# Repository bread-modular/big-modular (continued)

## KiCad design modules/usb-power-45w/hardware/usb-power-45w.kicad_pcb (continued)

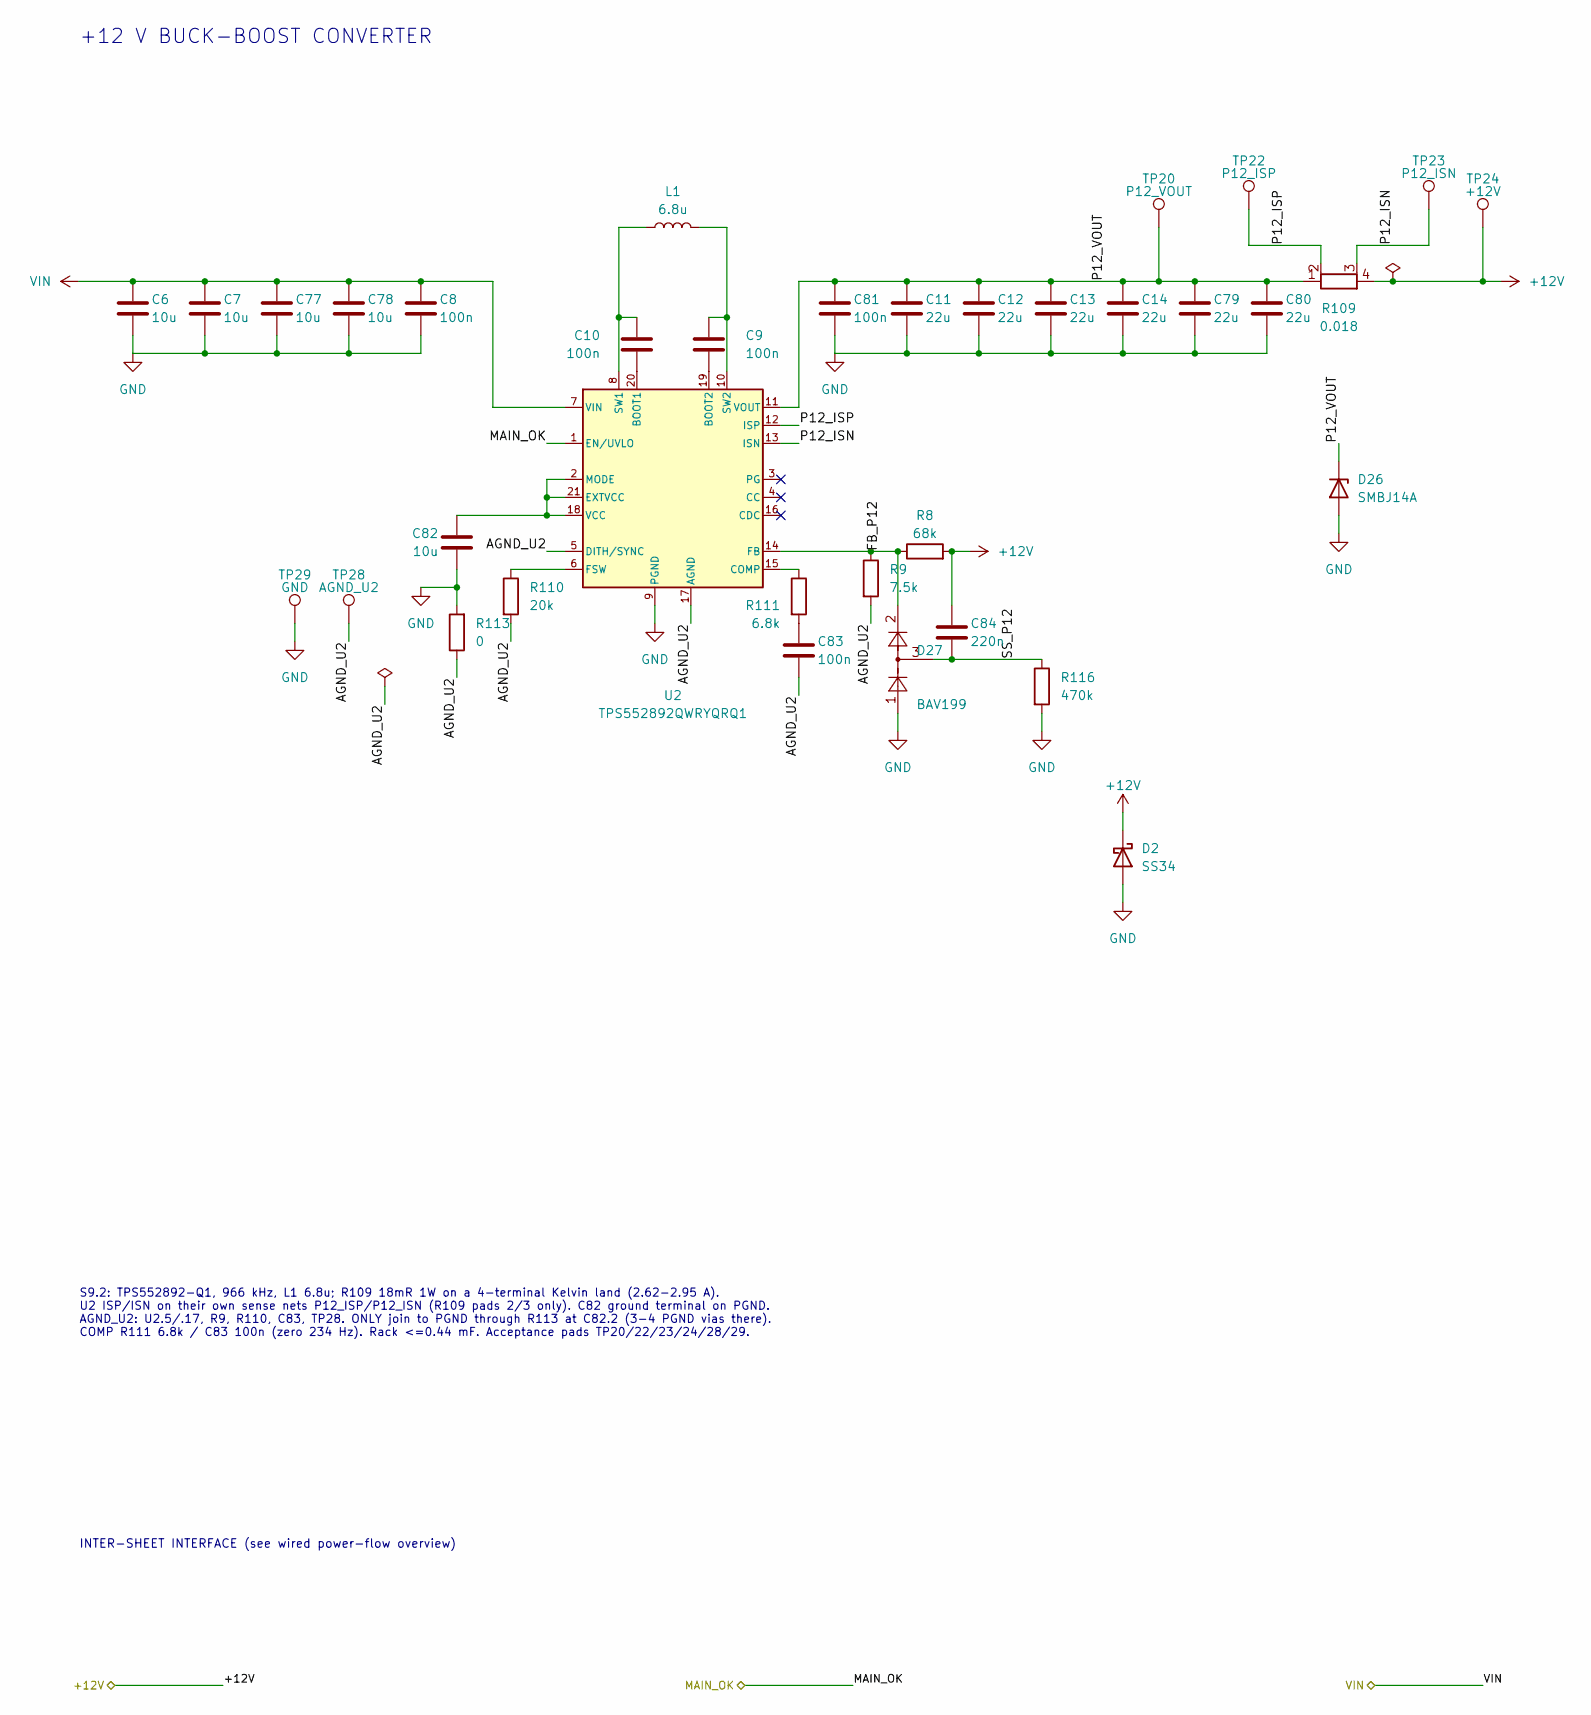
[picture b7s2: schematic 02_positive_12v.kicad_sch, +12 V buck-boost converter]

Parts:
C6, C7, C77, C78, C82: 10u; C_1206_3216Metric; Voltage 50V; MPN CL31A106KBHNNNE; LCSC C13585
C8, C9, C10, C81, C83: 100n; C_0603_1608Metric; Voltage 50V; MPN CC0603KRX7R9BB104; LCSC C14663
C11, C12, C13, C14, C79, C80: 22u; C_1206_3216Metric; Voltage 25V; MPN CL31A226KAHNNNE; LCSC C12891
C84: 220n; C_0603_1608Metric; Voltage 25V; MPN CL10B224KA8NNNC; LCSC C21120
D2: SS34; D_SMA; MPN SS34; LCSC C8678
D26: SMBJ14A; D_SMB; MPN SMBJ14A; LCSC C315990
D27: BAV199; SOT-23; MPN BAV199LT1G; LCSC C145516
L1: 6.8u; L_SLO1040H6R8MTT; MPN SLO1040H6R8MTT; LCSC C207852
R8: 68k; R_0603_1608Metric; Tolerance 1%; MPN 0603WAF6802T5E; LCSC C23231
R9: 7.5k; R_0603_1608Metric; Tolerance 1%; MPN 0603WAF7501T5E; LCSC C23234
R109: 0.018; R_Shunt_1206_KelvinSplit_RLM12; Tolerance 1%; MPN RLM12FTCMR018; LCSC C393095
R110: 20k; R_0603_1608Metric; Tolerance 1%; MPN 0603WAF2002T5E; LCSC C4184
R111: 6.8k; R_0603_1608Metric; Tolerance 1%; MPN 0603WAF6801T5E; LCSC C23212
R113: 0; R_0603_1608Metric; MPN 0603WAF0000T5E; LCSC C21189
R116: 470k; R_0603_1608Metric; Tolerance 1%; MPN 0603WAF4703T5E; LCSC C23178
TP20: P12_VOUT; TestPoint_Pad_D1.5mm
TP22: P12_ISP; TestPoint_Pad_D1.5mm
TP23: P12_ISN; TestPoint_Pad_D1.5mm
TP24: +12V; TestPoint_Pad_D1.5mm
TP28: AGND_U2; TestPoint_Pad_D1.5mm
TP29: GND; TestPoint_Pad_D1.5mm
U2: TPS552892QWRYQRQ1; TI_RYQ0021B_VQFN-HR-21_3x5mm; MPN TPS552892QWRYQRQ1; LCSC C22375748

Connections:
+12V: C84.1, D2.1 (K), R8.2, R109.4, TP24.1 (1_1); also elsewhere on the board
/+12 V buck-boost converter/AGND_U2: C83.2, R9.2, R110.2, R113.1, TP28.1 (1_1), U2.5 (DITH/SYNC), U2.17 (AGND)
/+12 V buck-boost converter/FB_P12: D27.2 (K), R8.1, R9.1, U2.14 (FB)
/+12 V buck-boost converter/P12_ISN: R109.3, TP23.1 (1_1), U2.13 (ISN)
/+12 V buck-boost converter/P12_ISP: R109.2, TP22.1 (1_1), U2.12 (ISP)
/+12 V buck-boost converter/P12_VOUT: C11.1, C12.1, C13.1, C14.1, C79.1, C80.1, C81.1, D26.1 (K), R109.1, TP20.1 (1_1), U2.11 (VOUT)
/+12 V buck-boost converter/SS_P12: C84.2, D27.3 (COM), R116.1
/MAIN_OK: U2.1 (EN/UVLO); also elsewhere on the board
GND: C6.2, C7.2, C8.2, C11.2, C12.2, C13.2, C14.2, C77.2, C78.2, C79.2, C80.2, C81.2, C82.2, D2.2 (A), D26.2 (A), D27.1 (A), R113.2, R116.2, TP29.1 (1_1), U2.9 (PGND); also elsewhere on the board
unnamed: C83.1, R111.2
unnamed: C10.1, U2.20 (BOOT1)
unnamed: C9.1, U2.19 (BOOT2)
unnamed: R111.1, U2.15 (COMP)
unnamed: C82.1, U2.2 (MODE), U2.18 (VCC), U2.21 (EXTVCC)
unnamed: R110.1, U2.6 (FSW)
unnamed: C10.2, L1.1, U2.8 (SW1)
unnamed: C9.2, L1.2, U2.10 (SW2)
VIN: C6.1, C7.1, C8.1, C77.1, C78.1, U2.7 (VIN); also elsewhere on the board

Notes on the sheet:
+12 V BUCK-BOOST CONVERTER
INTER-SHEET INTERFACE (see wired power-flow overview)
S9.2: TPS552892-Q1, 966 kHz, L1 6.8u; R109 18mR 1W on a 4-terminal Kelvin land (2.62-2.95 A). U2 ISP/ISN on their own sense nets P12_ISP/P12_ISN (R109 pads 2/3 only). C82 ground terminal on PGND. AGND_U2: U2.5/.17, R9, R110, C83, TP28. ONLY join to PGND through R113 at C82.2 (3-4 PGND vias there). 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

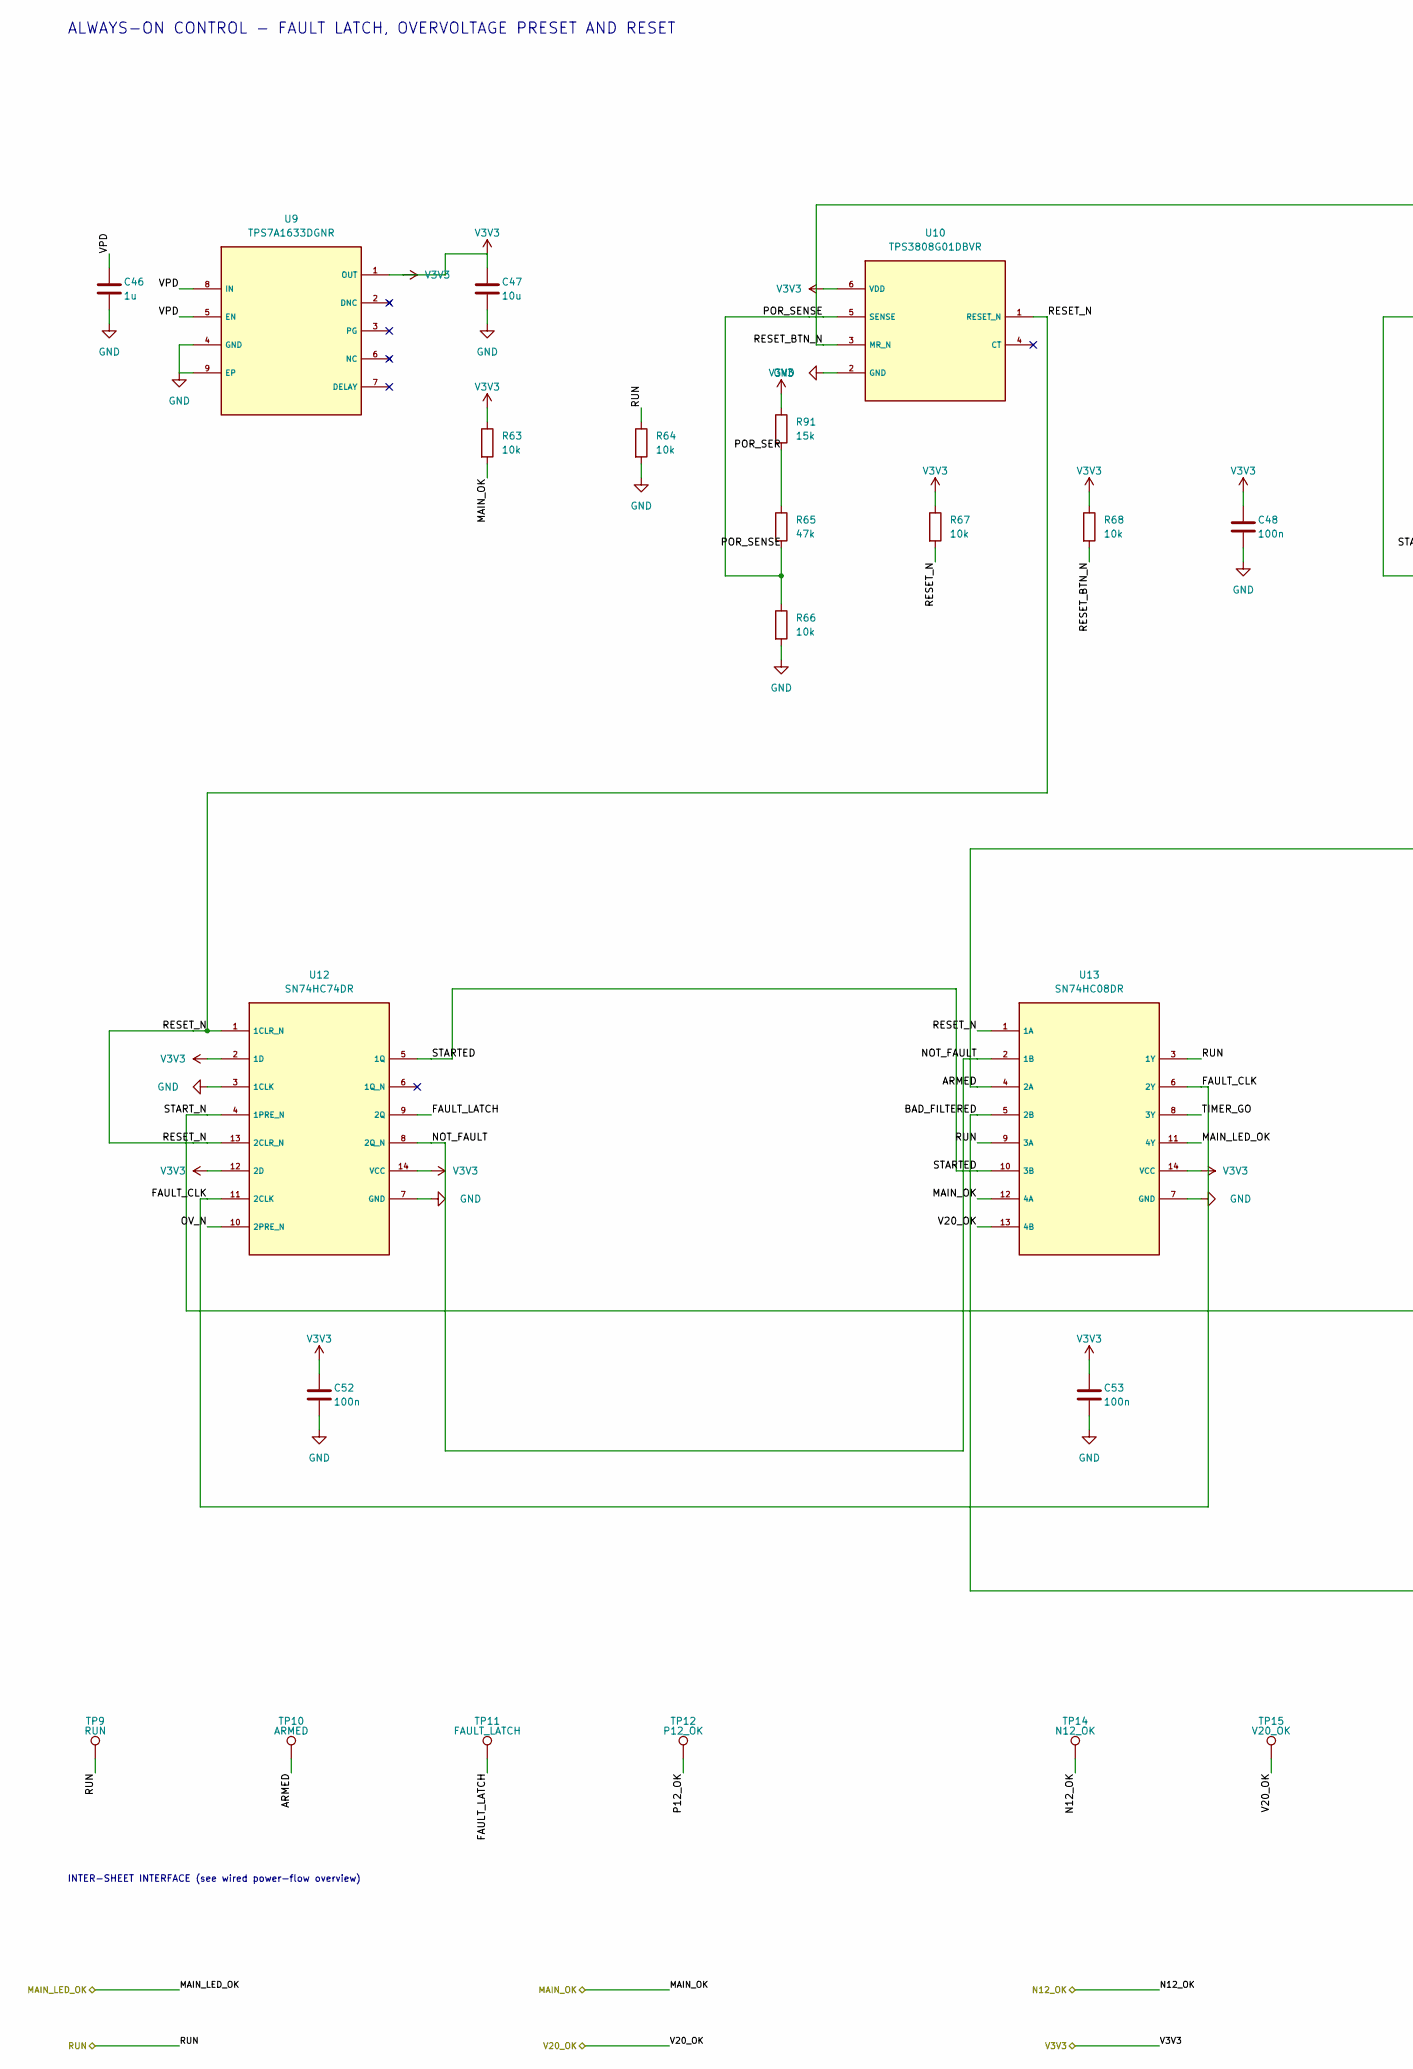
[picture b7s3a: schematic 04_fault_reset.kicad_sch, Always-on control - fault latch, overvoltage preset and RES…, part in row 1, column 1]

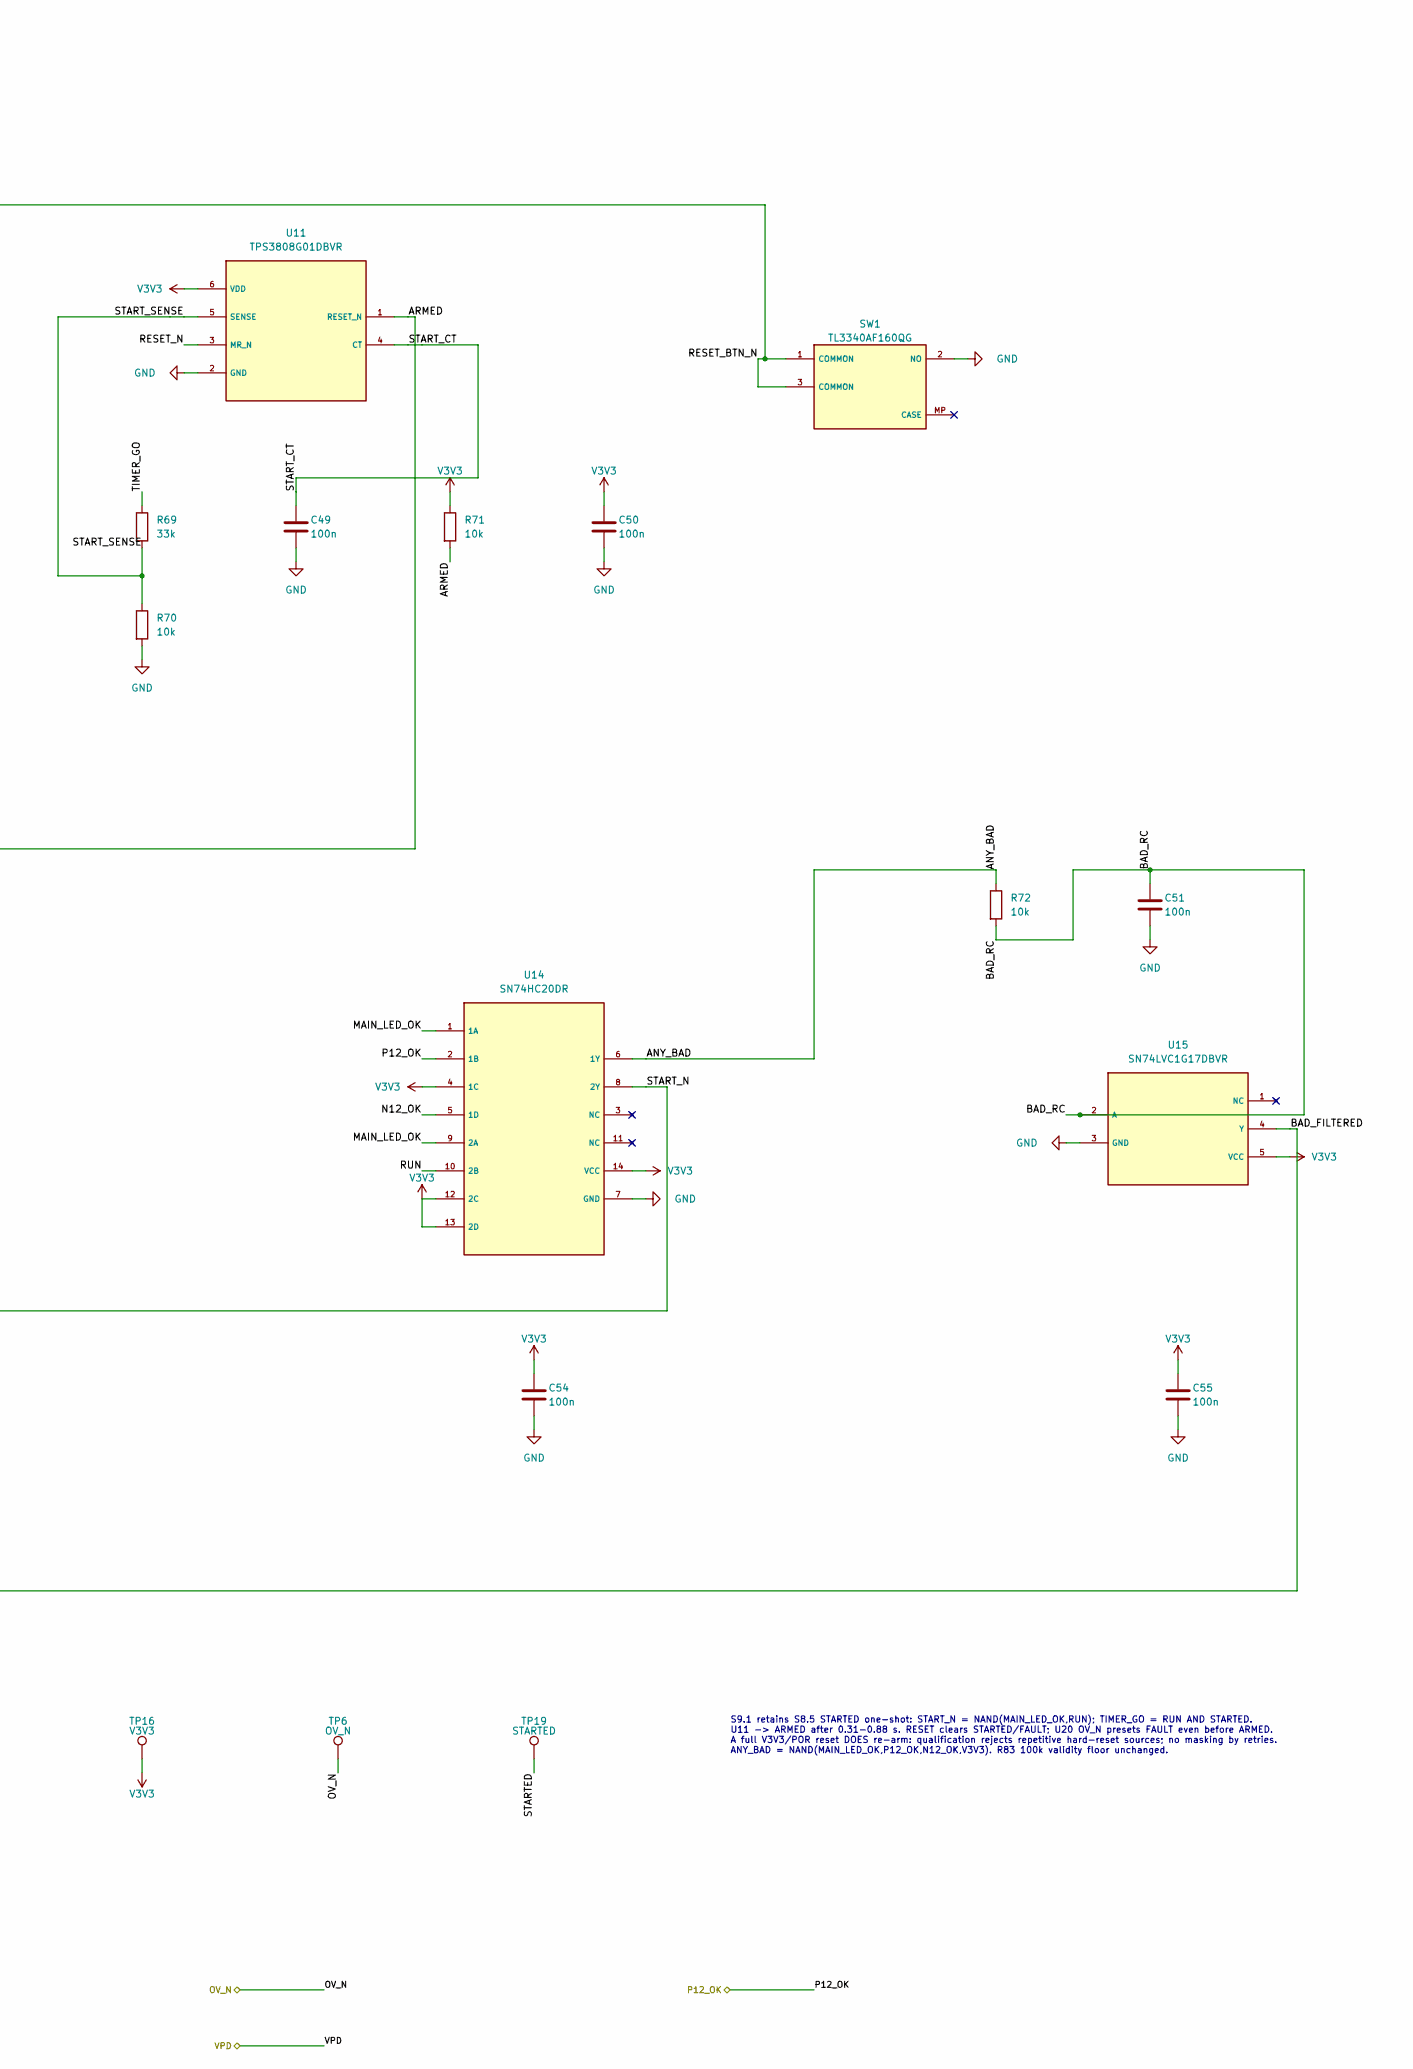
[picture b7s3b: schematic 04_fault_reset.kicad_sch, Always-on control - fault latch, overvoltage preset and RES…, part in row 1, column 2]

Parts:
C46: 1u; C_0603_1608Metric; Voltage 50V; MPN CL10A105KB8NNNC; LCSC C15849
C47: 10u; C_1206_3216Metric; Voltage 50V; MPN CL31A106KBHNNNE; LCSC C13585
C48, C49, C50, C51, C52, C53, C54, C55: 100n; C_0603_1608Metric; Voltage 50V; MPN CC0603KRX7R9BB104; LCSC C14663
R63, R64, R66, R67, R68, R70, R71, R72: 10k; R_0603_1608Metric; Tolerance 1%; MPN 0603WAF1002T5E; LCSC C25804
R65: 47k; R_0603_1608Metric; Tolerance 1%; MPN 0603WAF4702T5E; LCSC C25819
R69: 33k; R_0603_1608Metric; Tolerance 1%; MPN 0603WAF3302T5E; LCSC C4216
R91: 15k; R_0603_1608Metric; Tolerance 1%; MPN 0603WAF1502T5E; LCSC C22809
SW1: TL3340AF160QG; SW_TL3340AF160QG_HandSolder; MPN TL3340AF160QG; LCSC C2886925
TP6: OV_N; TestPoint_Pad_D1.0mm
TP9: RUN; TestPoint_Pad_D1.0mm
TP10: ARMED; TestPoint_Pad_D1.0mm
TP11: FAULT_LATCH; TestPoint_Pad_D1.0mm
TP12: P12_OK; TestPoint_Pad_D1.0mm
TP14: N12_OK; TestPoint_Pad_D1.0mm
TP15: V20_OK; TestPoint_Pad_D1.0mm
TP16: V3V3; TestPoint_Pad_D1.0mm
TP19: STARTED; TestPoint_Pad_D1.0mm
U9: TPS7A1633DGNR; TPS7A16_DGN0008C_NoViaInPad; MPN TPS7A1633DGNR; LCSC C181239
U10, U11: TPS3808G01DBVR; SOT-23-6; MPN TPS3808G01DBVR; LCSC C19653
U12: SN74HC74DR; SOIC-14_3.9x8.7mm_P1.27mm; MPN SN74HC74DR; LCSC C6762
U13: SN74HC08DR; SOIC-14_3.9x8.7mm_P1.27mm; MPN SN74HC08DR; LCSC C337768
U14: SN74HC20DR; SOIC-14_3.9x8.7mm_P1.27mm; MPN SN74HC20DR; LCSC C2867684
U15: SN74LVC1G17DBVR; SOT-23-5; MPN SN74LVC1G17DBVR; LCSC C7836

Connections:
/Always-on control - fault latch, overvoltage preset and RESET/ANY_BAD: R72.1, U14.6 (1Y)
/Always-on control - fault latch, overvoltage preset and RESET/ARMED: R71.2, TP10.1 (1_1), U11.1 (RESET_N), U13.4 (2A)
/Always-on control - fault latch, overvoltage preset and RESET/BAD_FILTERED: U13.5 (2B), U15.4 (Y)
/Always-on control - fault latch, overvoltage preset and RESET/BAD_RC: C51.1, R72.2, U15.2 (A)
/Always-on control - fault latch, overvoltage preset and RESET/FAULT_CLK: U12.11 (2CLK), U13.6 (2Y)
/Always-on control - fault latch, overvoltage preset and RESET/FAULT_LATCH: TP11.1 (1_1), U12.9 (2Q)
/Always-on control - fault latch, overvoltage preset and RESET/NOT_FAULT: U12.8 (2Q_N), U13.2 (1B)
/Always-on control - fault latch, overvoltage preset and RESET/POR_SENSE: R65.2, R66.1, U10.5 (SENSE)
/Always-on control - fault latch, overvoltage preset and RESET/POR_SER: R65.1, R91.2
/Always-on control - fault latch, overvoltage preset and RESET/RESET_BTN_N: R68.2, SW1.1 (COMMON), SW1.3 (COMMON), U10.3 (MR_N)
/Always-on control - fault latch, overvoltage preset and RESET/RESET_N: R67.2, U10.1 (RESET_N), U11.3 (MR_N), U12.1 (1CLR_N), U12.13 (2CLR_N), U13.1 (1A)
/Always-on control - fault latch, overvoltage preset and RESET/STARTED: TP19.1 (1_1), U12.5 (1Q), U13.10 (3B)
/Always-on control - fault latch, overvoltage preset and RESET/START_CT: C49.1, U11.4 (CT)
/Always-on control - fault latch, overvoltage preset and RESET/START_N: U12.4 (1PRE_N), U14.8 (2Y)
/Always-on control - fault latch, overvoltage preset and RESET/START_SENSE: R69.2, R70.1, U11.5 (SENSE)
/Always-on control - fault latch, overvoltage preset and RESET/TIMER_GO: R69.1, U13.8 (3Y)
/MAIN_LED_OK: U13.11 (4Y), U14.1 (1A), U14.9 (2A); also elsewhere on the board
/MAIN_OK: R63.2, U13.12 (4A); also elsewhere on the board
/N12_OK: TP14.1 (1_1), U14.5 (1D); also elsewhere on the board
/OV_N: TP6.1 (1_1), U12.10 (2PRE_N); also elsewhere on the board
/P12_OK: TP12.1 (1_1), U14.2 (1B); also elsewhere on the board
/RUN: R64.1, TP9.1 (1_1), U13.3 (1Y), U13.9 (3A), U14.10 (2B); also elsewhere on the board
/V20_OK: TP15.1 (1_1), U13.13 (4B); also elsewhere on the board
/VPD: C46.1, U9.5 (EN), U9.8 (IN); also elsewhere on the board
GND: C46.2, C47.2, C48.2, C49.2, C50.2, C51.2, C52.2, C53.2, C54.2, C55.2, R64.2, R66.2, R70.2, SW1.2 (NO), U9.4 (GND), U9.9 (EP), U10.2 (GND), U11.2 (GND), U12.3 (1CLK), U12.7 (GND), U13.7 (GND), U14.7 (GND), U15.3 (GND); also elsewhere on the board
V3V3: C47.1, C48.1, C50.1, C52.1, C53.1, C54.1, C55.1, R63.1, R67.1, R68.1, R71.1, R91.1, TP16.1 (1_1), U9.1 (OUT), U10.6 (VDD), U11.6 (VDD), U12.2 (1D), U12.12 (2D), U12.14 (VCC), U13.14 (VCC), U14.4 (1C), U14.12 (2C), U14.13 (2D), U14.14 (VCC), U15.5 (VCC); also elsewhere on the board

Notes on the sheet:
ALWAYS-ON CONTROL - FAULT LATCH, OVERVOLTAGE PRESET AND RESET
INTER-SHEET INTERFACE (see wired power-flow overview)
S9.1 retains S8.5 STARTED one-shot: START_N = NAND(MAIN_LED_OK,RUN); TIMER_GO = RUN AND STARTED. U11 -> ARMED after 0.31-0.88 s. RESET clears STARTED/FAULT; U20 OV_N presets FAULT even before ARMED. A full V3V3/POR reset DOES re-arm: qualification rejects repetitive hard-reset sources; no masking b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

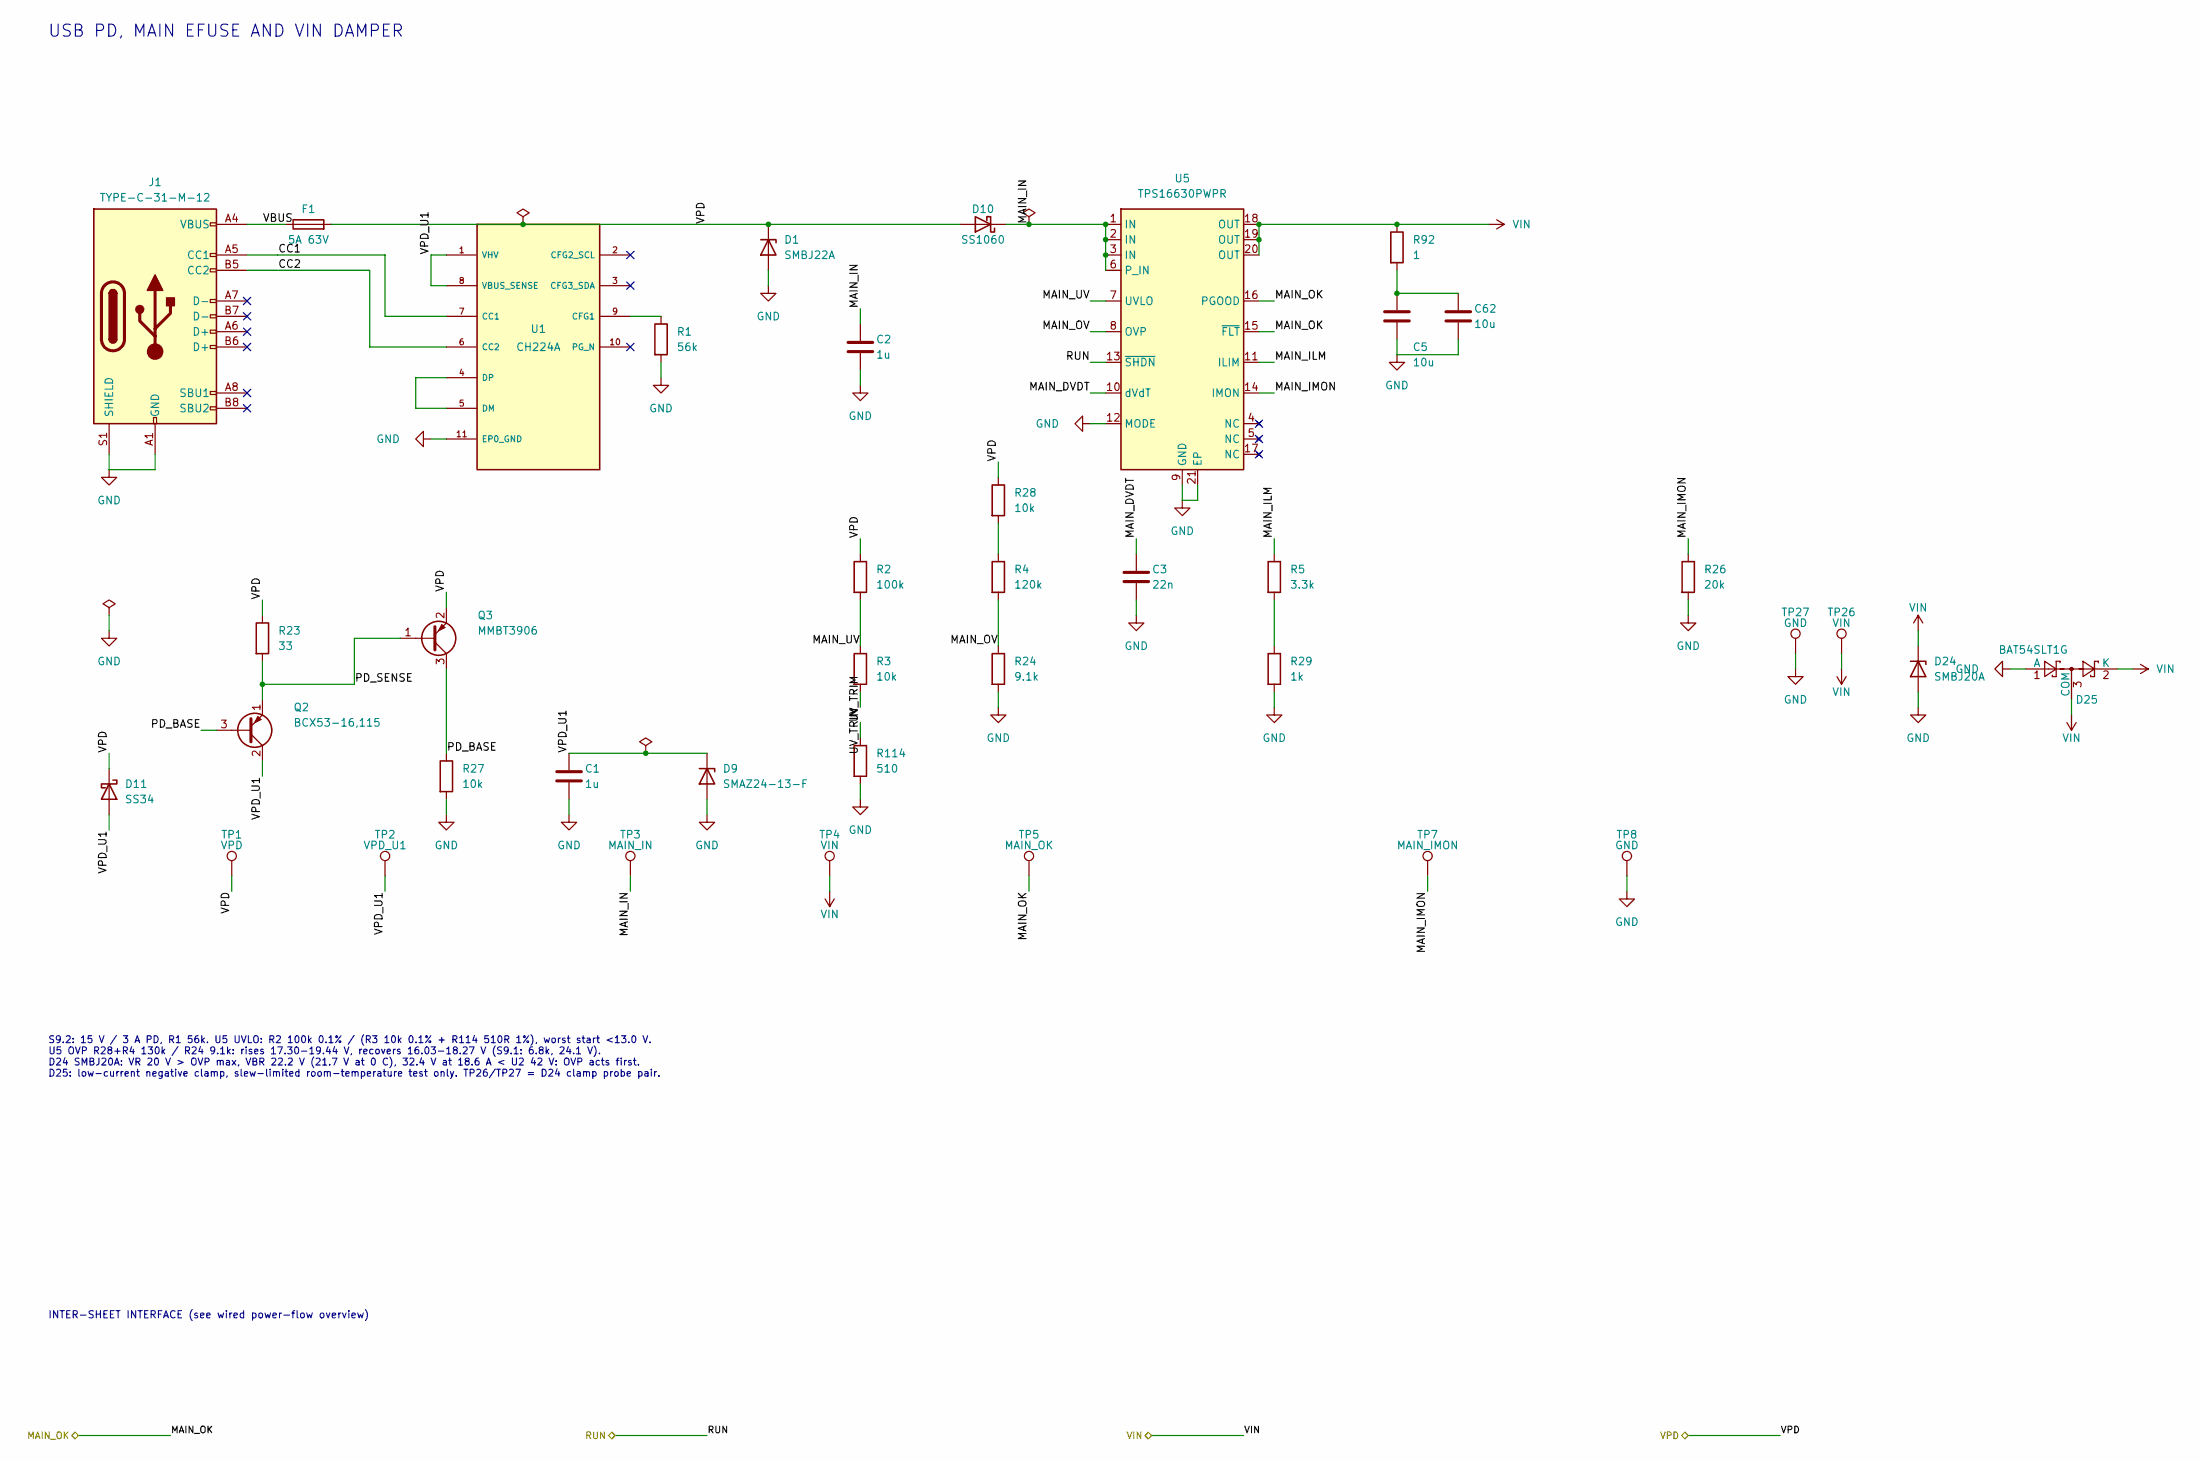
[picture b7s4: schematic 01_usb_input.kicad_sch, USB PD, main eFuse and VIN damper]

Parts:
C1, C2: 1u; C_0603_1608Metric; Voltage 50V; MPN CL10A105KB8NNNC; LCSC C15849
C3: 22n; C_0603_1608Metric; Voltage 50V; MPN CL10B223KB8NNNC; LCSC C21122
C5, C62: 10u; C_1206_3216Metric; Voltage 50V; MPN CL31A106KBHNNNE; LCSC C13585
D1: SMBJ22A; D_SMB; MPN SMBJ22A; LCSC C224015
D9: SMAZ24-13-F; D_SMA; MPN SMAZ24-13-F; LCSC C155317
D10: SS1060; D_SMC; MPN SS1060; LCSC C2917888
D11: SS34; D_SMA; MPN SS34; LCSC C8678
D24: SMBJ20A; D_SMB; MPN SMBJ20A; LCSC C151257
D25: BAT54SLT1G; SOT-23; MPN BAT54SLT1G; LCSC C19726
F1: 5A 63V; Fuse_1206_3216Metric; MPN S1206-SD-5.0A; LCSC C553937
J1: TYPE-C-31-M-12; HRO-TYPE-C-31-M-12; MPN TYPE-C-31-M-12; LCSC C165948
Q2: BCX53-16,115; SOT-89-3; MPN BCX53-16,115; LCSC C47787
Q3: MMBT3906; SOT-23; MPN MMBT3906LT1G; LCSC C53444
R1: 56k; R_0603_1608Metric; Tolerance 1%; MPN 0603WAF5602T5E; LCSC C23206
R2: 100k; R_0603_1608Metric; Tolerance 0.1%; MPN RT0603BRD07100KL; LCSC C122538
R3: 10k; R_0603_1608Metric; Tolerance 0.1%; MPN RT0603BRD0710KL; LCSC C95204
R4: 120k; R_0603_1608Metric; Tolerance 1%; MPN 0603WAF1203T5E; LCSC C25808
R5: 3.3k; R_0603_1608Metric; Tolerance 1%; MPN 0603WAF3301T5E; LCSC C22978
R23: 33; R_0603_1608Metric; Tolerance 1%; MPN 0603WAF330JT5E; LCSC C23140
R24: 9.1k; R_0603_1608Metric; Tolerance 1%; MPN 0603WAF9101T5E; LCSC C23260
R26: 20k; R_0603_1608Metric; Tolerance 1%; MPN 0603WAF2002T5E; LCSC C4184
R27: 10k; R_1206_3216Metric; Tolerance 1%; MPN 1206W4F1002T5E; LCSC C17902
R28: 10k; R_0603_1608Metric; Tolerance 1%; MPN 0603WAF1002T5E; LCSC C25804
R29: 1k; R_0603_1608Metric; Tolerance 1%; MPN 0603WAF1001T5E; LCSC C21190
R92: 1; R_1206_3216Metric; Tolerance 1%; MPN 1206W4F100KT5E; LCSC C17928
R114: 510; R_0603_1608Metric; Tolerance 1%; MPN 0603WAF5100T5E; LCSC C23193
TP1: VPD; TestPoint_Pad_D1.0mm
TP2: VPD_U1; TestPoint_Pad_D1.0mm
TP3: MAIN_IN; TestPoint_Pad_D1.0mm
TP4: VIN; TestPoint_Pad_D1.0mm
TP5: MAIN_OK; TestPoint_Pad_D1.0mm
TP7: MAIN_IMON; TestPoint_Pad_D1.0mm
TP8: GND; TestPoint_Pad_D1.0mm
TP26: VIN; TestPoint_Pad_D1.5mm
TP27: GND; TestPoint_Pad_D1.5mm
U1: CH224A; SSOP-10-1EP_3.9x4.9mm_P1mm_EP2.1x3.3mm; MPN CH224A; LCSC C42459160
U5: TPS16630PWPR; HTSSOP-20-1EP_4.4x6.5mm_P0.65mm_EP3.4x6.5mm_Mask2.96x2.96mm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; MPN TPS16630PWPR; LCSC C1849461

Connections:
/MAIN_OK: TP5.1 (1_1), U5.15 (~FLT), U5.16 (PGOOD); also elsewhere on the board
/RUN: U5.13 (~SHDN); also elsewhere on the board
/USB PD, main eFuse and VIN damper/CC1: J1.A5 (CC1), U1.7 (CC1)
/USB PD, main eFuse and VIN damper/CC2: J1.B5 (CC2), U1.6 (CC2)
/USB PD, main eFuse and VIN damper/MAIN_DVDT: C3.1, U5.10 (dVdT)
/USB PD, main eFuse and VIN damper/MAIN_ILM: R5.1, U5.11 (ILIM)
/USB PD, main eFuse and VIN damper/MAIN_IMON: R26.1, TP7.1 (1_1), U5.14 (IMON)
/USB PD, main eFuse and VIN damper/MAIN_IN: C2.1, D10.1 (K), TP3.1 (1_1), U5.1 (IN), U5.2 (IN), U5.3 (IN), U5.6 (P_IN)
/USB PD, main eFuse and VIN damper/MAIN_OV: R4.2, R24.1, U5.8 (OVP)
/USB PD, main eFuse and VIN damper/MAIN_UV: R2.2, R3.1, U5.7 (UVLO)
/USB PD, main eFuse and VIN damper/PD_BASE: Q2.3 (B), Q3.3 (C), R27.1
/USB PD, main eFuse and VIN damper/PD_SENSE: Q2.1 (E), Q3.1 (B), R23.2
/USB PD, main eFuse and VIN damper/UV_TRIM: R3.2, R114.1
/USB PD, main eFuse and VIN damper/VBUS: F1.1, J1.A4 (VBUS), J1.A9 (VBUS)
/USB PD, main eFuse and VIN damper/VPD_U1: C1.1, D9.1 (K), D11.2 (A), Q2.2 (C), TP2.1 (1_1), U1.1 (VHV), U1.8 (VBUS_SENSE)
/VPD: D1.1 (K), D10.2 (A), D11.1 (K), F1.2, Q3.2 (E), R2.1, R23.1, R28.1, TP1.1 (1_1); also elsewhere on the board
GND: C1.2, C2.2, C3.2, C5.2, C62.2, D1.2 (A), D9.2 (A), D24.2 (A), D25.1 (A), J1.A1 (GND), J1.A12 (GND), J1.S1 (SHIELD), R1.2, R24.2, R26.2, R27.2, R29.2, R114.2, TP8.1 (1_1), TP27.1 (1_1), U1.11 (EP0_GND), U5.9 (GND), U5.12 (MODE), U5.21 (EP); also elsewhere on the board
unnamed: C5.1, C62.1, R92.2
unnamed: R4.1, R28.2
unnamed: R5.2, R29.1
unnamed: R1.1, U1.9 (CFG1)
unnamed: U1.4 (DP), U1.5 (DM)
VIN: D24.1 (K), D25.2 (K), D25.3 (COM), R92.1, TP4.1 (1_1), TP26.1 (1_1), U5.18 (OUT), U5.19 (OUT), U5.20 (OUT); also elsewhere on the board

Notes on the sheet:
USB PD, MAIN EFUSE AND VIN DAMPER
INTER-SHEET INTERFACE (see wired power-flow overview)
S9.2: 15 V / 3 A PD, R1 56k. U5 UVLO: R2 100k 0.1% / (R3 10k 0.1% + R114 510R 1%), worst start <13.0 V. U5 OVP R28+R4 130k / R24 9.1k: rises 17.30-19.44 V, recovers 16.03-18.27 V (S9.1: 6.8k, 24.1 V). D24 SMBJ20A: VR 20 V > OVP max, VBR 22.2 V (21.7 V at 0 C), 32.4 V at 18.6 A < U2 42 V: OVP acts f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
